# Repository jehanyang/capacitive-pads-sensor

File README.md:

# :arrow_heading_up: Capacitive Pads Sensor
Kicad files to make a custom capacitive pads sensor. Uses standard male header pins with 0.1 inch pitch, so can be directly inserted into many capacitive breakout boards. 

This board was ordered through AllPCB, which has flexible PCB capabilities. The following shows dimensioning to ensure equal pad spacing. Dimensioning also occurs for the stiffeners.

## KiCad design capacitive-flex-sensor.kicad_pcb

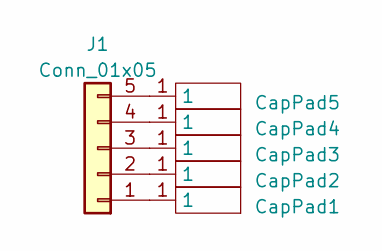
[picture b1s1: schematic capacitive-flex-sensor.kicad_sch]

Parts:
CapPad1, CapPad2, CapPad3, CapPad4, CapPad5: capacitive_pad_20x20
J1: Conn_01x05; PinHeader_1x05_P2.54mm_Vertical

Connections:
unnamed: CapPad1.1, J1.1
unnamed: CapPad2.1, J1.2
unnamed: CapPad3.1, J1.3
unnamed: CapPad4.1, J1.4
unnamed: CapPad5.1, J1.5

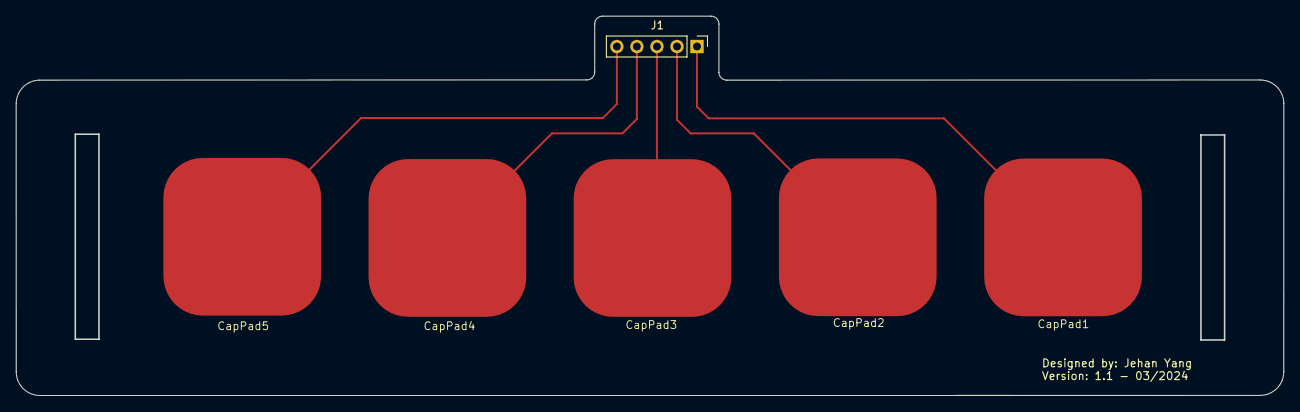
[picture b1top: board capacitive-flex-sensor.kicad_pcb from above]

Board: 2 copper layers, 160.6 x 48.0 mm, 6 parts (0 on the bottom side), 5 nets.

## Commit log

2024-03-20 feat: first import, first version with 12 electrodes
2024-03-20 chore: change README.md to get rid of template info
2024-03-21 feat: new version with 5 pads and pins on top
2024-03-21 chore: add screenshot
2024-03-21 chore: change version number on layout
2024-03-21 debug: modified dimension labels to add stiffener thicknesses
2024-03-27 docs: added dimensions for stiffeners
